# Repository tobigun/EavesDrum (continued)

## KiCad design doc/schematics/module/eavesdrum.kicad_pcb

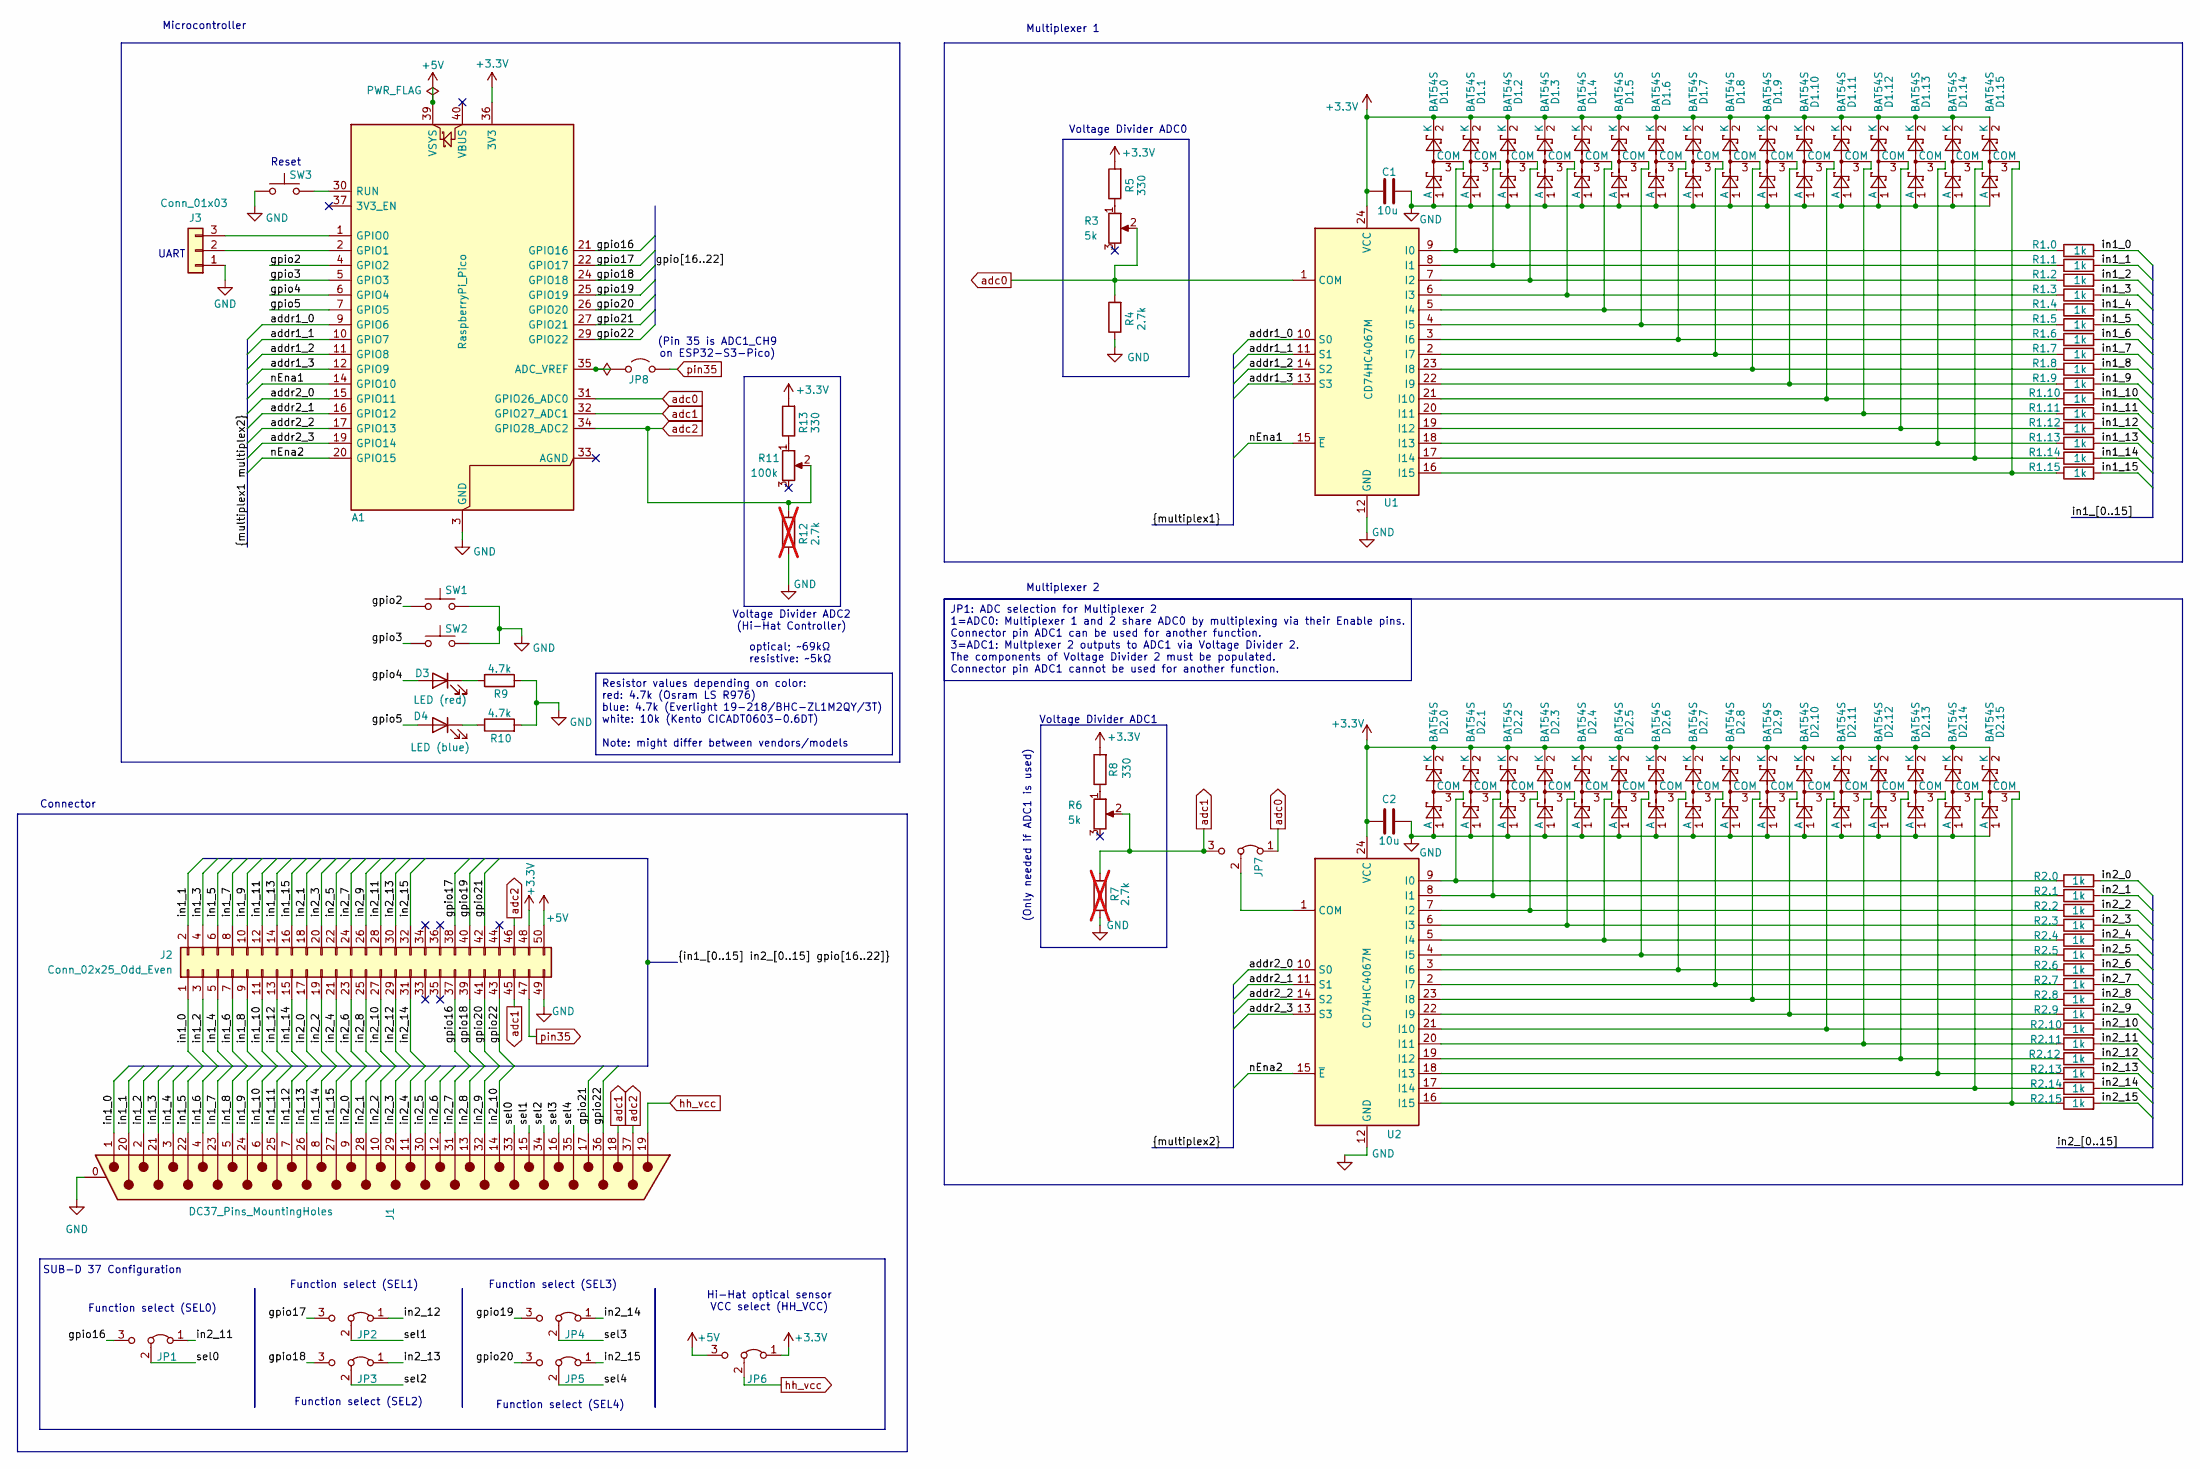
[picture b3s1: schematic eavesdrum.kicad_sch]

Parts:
A1: RaspberryPi_Pico; RaspberryPi_Pico_Common_Unspecified; LCSC C41407547
C1, C2: 10u; C_0805_2012Metric
D1.0, D1.1, D1.2, D1.3, D1.4, D1.5, D1.6, D1.7, D1.8, D1.9, D1.10, D1.11, D1.12, D1.13, D1.14, D1.15, D2.0, D2.1, D2.2, D2.3, D2.4, D2.5, D2.6, D2.7, D2.8, D2.9, D2.10, D2.11, D2.12, D2.13, D2.14, D2.15: BAT54S; SOT-23
D3: LED (red); LED_D3.0mm
D4: LED (blue); LED_D3.0mm
J1: DC37_Pins_MountingHoles; DSUB-37_Pins_Horizontal_P2.77x2.84mm_EdgePinOffset7.70mm_Ho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
J2: Conn_02x25_Odd_Even; IDC-Header_2x25_P2.54mm_Vertical_SMD; LCSC C383615
J3: Conn_01x03; PinSocket_1x03_P2.54mm_Vertical_SMD_Pin1Left
JP1, JP2, JP3, JP4, JP5, JP6: Jumper; PinHeader_1x03_P2.54mm_Vertical_SMD_Pin1Right; LCSC C2875122
JP7: Jumper_3; SolderJumper-3_P1.3mm_Bridged12_RoundedPad1.0x1.5mm_NumberL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
JP8: Jumper_2_Open; SolderJumper-2_P1.3mm_Open_RoundedPad1.0x1.5mm
R1.0, R1.1, R1.2, R1.3, R1.4, R1.5, R1.6, R1.7, R1.8, R1.9, R1.10, R1.11, R1.12, R1.13, R1.14, R1.15, R2.0, R2.1, R2.2, R2.3, R2.4, R2.5, R2.6, R2.7, R2.8, R2.9, R2.10, R2.11, R2.12, R2.13, R2.14, R2.15: 1k; R_0805_2012Metric
R3, R6: 5k; Potentiometer_Bourns_TC33X_Vertical
R4: 2.7k; R_0805_2012Metric
R5, R8, R13: 330; R_0805_2012Metric
R7, R12: 2.7k; R_0805_2012Metric; not fitted
R9, R10: 4.7k; R_0805_2012Metric
R11: 100k; Potentiometer_Bourns_TC33X_Vertical
SW1, SW2, SW3: SW_Push; SW_Push_1P1T_NO_CK_KSC6xxJ
U1: CD74HC4067M; SOIC-24W_7.5x15.4mm_P1.27mm
U2: CD74HC4067M; SOIC-24W_7.5x15.4mm_P1.27mm; LCSC C1545936

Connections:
+3.3V: A1.36 (3V3), C1.1, C2.1, D1.0.2 (K), D1.1.2 (K), D1.2.2 (K), D1.3.2 (K), D1.4.2 (K), D1.5.2 (K), D1.6.2 (K), D1.7.2 (K), D1.8.2 (K), D1.9.2 (K), D1.10.2 (K), D1.11.2 (K), D1.12.2 (K), D1.13.2 (K), D1.14.2 (K), D1.15.2 (K), D2.0.2 (K), D2.1.2 (K), D2.2.2 (K), D2.3.2 (K), D2.4.2 (K), D2.5.2 (K), D2.6.2 (K), D2.7.2 (K), D2.8.2 (K), D2.9.2 (K), D2.10.2 (K), D2.11.2 (K), D2.12.2 (K), D2.13.2 (K), D2.14.2 (K), D2.15.2 (K), J2.48, JP6.1 (A), R5.2, R8.2, R13.2, U1.24 (VCC), U2.24 (VCC)
+5V: A1.39 (VSYS), J2.50, JP6.3 (B)
/addr1_0: A1.9 (GPIO6), U1.10 (S0)
/addr1_1: A1.10 (GPIO7), U1.11 (S1)
/addr1_2: A1.11 (GPIO8), U1.14 (S2)
/addr1_3: A1.12 (GPIO9), U1.13 (S3)
/addr2_0: A1.15 (GPIO11), U2.10 (S0)
/addr2_1: A1.16 (GPIO12), U2.11 (S1)
/addr2_2: A1.17 (GPIO13), U2.14 (S2)
/addr2_3: A1.19 (GPIO14), U2.13 (S3)
/gpio2: A1.4 (GPIO2), SW1.1
/gpio3: A1.5 (GPIO3), SW2.1
/gpio4: A1.6 (GPIO4), D3.2 (A)
/gpio5: A1.7 (GPIO5), D4.2 (A)
/gpio16: A1.21 (GPIO16), J2.37, JP1.3 (B)
/gpio17: A1.22 (GPIO17), J2.38, JP2.3 (B)
/gpio18: A1.24 (GPIO18), J2.39, JP3.3 (B)
/gpio19: A1.25 (GPIO19), J2.40, JP4.3 (B)
/gpio20: A1.26 (GPIO20), J2.41, JP5.3 (B)
/gpio21: A1.27 (GPIO21), J1.17, J2.42
/gpio22: A1.29 (GPIO22), J1.36, J2.43
/in1_0: J1.1, J2.1, R1.0.2
/in1_1: J1.20, J2.2, R1.1.2
/in1_2: J1.2, J2.3, R1.2.2
/in1_3: J1.21, J2.4, R1.3.2
/in1_4: J1.3, J2.5, R1.4.2
/in1_5: J1.22, J2.6, R1.5.2
/in1_6: J1.4, J2.7, R1.6.2
/in1_7: J1.23, J2.8, R1.7.2
/in1_8: J1.5, J2.9, R1.8.2
/in1_9: J1.24, J2.10, R1.9.2
/in1_10: J1.6, J2.11, R1.10.2
/in1_11: J1.25, J2.12, R1.11.2
/in1_12: J1.7, J2.13, R1.12.2
/in1_13: J1.26, J2.14, R1.13.2
/in1_14: J1.8, J2.15, R1.14.2
/in1_15: J1.27, J2.16, R1.15.2
/in2_0: J1.9, J2.17, R2.0.2
/in2_1: J1.28, J2.18, R2.1.2
/in2_2: J1.10, J2.19, R2.2.2
/in2_3: J1.29, J2.20, R2.3.2
/in2_4: J1.11, J2.21, R2.4.2
/in2_5: J1.30, J2.22, R2.5.2
/in2_6: J1.12, J2.23, R2.6.2
/in2_7: J1.31, J2.24, R2.7.2
/in2_8: J1.13, J2.25, R2.8.2
/in2_9: J1.32, J2.26, R2.9.2
/in2_10: J1.14, J2.27, R2.10.2
/in2_11: J2.28, JP1.1 (A), R2.11.2
/in2_12: J2.29, JP2.1 (A), R2.12.2
/in2_13: J2.30, JP3.1 (A), R2.13.2
/in2_14: J2.31, JP4.1 (A), R2.14.2
/in2_15: J2.32, JP5.1 (A), R2.15.2
/nEna1: A1.14 (GPIO10), U1.15 (~E)
/nEna2: A1.20 (GPIO15), U2.15 (~E)
/sel0: J1.33, JP1.2 (C)
/sel1: J1.15, JP2.2 (C)
/sel2: J1.34, JP3.2 (C)
/sel3: J1.16, JP4.2 (C)
/sel4: J1.35, JP5.2 (C)
GND: A1.3 (GND), A1.8 (GND), A1.13 (GND), A1.18 (GND), A1.23 (GND), A1.28 (GND), A1.38 (GND), C1.2, C2.2, D1.0.1 (A), D1.1.1 (A), D1.2.1 (A), D1.3.1 (A), D1.4.1 (A), D1.5.1 (A), D1.6.1 (A), D1.7.1 (A), D1.8.1 (A), D1.9.1 (A), D1.10.1 (A), D1.11.1 (A), D1.12.1 (A), D1.13.1 (A), D1.14.1 (A), D1.15.1 (A), D2.0.1 (A), D2.1.1 (A), D2.2.1 (A), D2.3.1 (A), D2.4.1 (A), D2.5.1 (A), D2.6.1 (A), D2.7.1 (A), D2.8.1 (A), D2.9.1 (A), D2.10.1 (A), D2.11.1 (A), D2.12.1 (A), D2.13.1 (A), D2.14.1 (A), D2.15.1 (A), J1.0 (PAD), J2.49, J3.1, R4.1, R7.1, R9.2, R10.2, R12.1, SW1.2, SW2.2, SW3.1, U1.12 (GND), U2.12 (GND)
unnamed: A1.35 (ADC_VREF), JP8.1 (A)
unnamed: A1.1 (GPIO0), J3.3
unnamed: A1.2 (GPIO1), J3.2
unnamed: A1.30 (RUN), SW3.2
unnamed: D1.0.3 (COM), R1.0.1, U1.9 (I0)
unnamed: D1.1.3 (COM), R1.1.1, U1.8 (I1)
unnamed: D1.2.3 (COM), R1.2.1, U1.7 (I2)
unnamed: D1.3.3 (COM), R1.3.1, U1.6 (I3)
unnamed: D1.4.3 (COM), R1.4.1, U1.5 (I4)
unnamed: D1.5.3 (COM), R1.5.1, U1.4 (I5)
unnamed: D1.6.3 (COM), R1.6.1, U1.3 (I6)
unnamed: D1.7.3 (COM), R1.7.1, U1.2 (I7)
unnamed: D1.8.3 (COM), R1.8.1, U1.23 (I8)
unnamed: D1.9.3 (COM), R1.9.1, U1.22 (I9)
unnamed: D1.10.3 (COM), R1.10.1, U1.21 (I10)
unnamed: D1.11.3 (COM), R1.11.1, U1.20 (I11)
unnamed: D1.12.3 (COM), R1.12.1, U1.19 (I12)
unnamed: D1.13.3 (COM), R1.13.1, U1.18 (I13)
unnamed: D1.14.3 (COM), R1.14.1, U1.17 (I14)
unnamed: D1.15.3 (COM), R1.15.1, U1.16 (I15)
unnamed: D2.0.3 (COM), R2.0.1, U2.9 (I0)
unnamed: D2.1.3 (COM), R2.1.1, U2.8 (I1)
unnamed: D2.2.3 (COM), R2.2.1, U2.7 (I2)
unnamed: D2.3.3 (COM), R2.3.1, U2.6 (I3)
unnamed: D2.4.3 (COM), R2.4.1, U2.5 (I4)
unnamed: D2.5.3 (COM), R2.5.1, U2.4 (I5)
unnamed: D2.6.3 (COM), R2.6.1, U2.3 (I6)
unnamed: D2.7.3 (COM), R2.7.1, U2.2 (I7)
unnamed: D2.8.3 (COM), R2.8.1, U2.23 (I8)
unnamed: D2.9.3 (COM), R2.9.1, U2.22 (I9)
unnamed: D2.10.3 (COM), R2.10.1, U2.21 (I10)
unnamed: D2.11.3 (COM), R2.11.1, U2.20 (I11)
unnamed: D2.12.3 (COM), R2.12.1, U2.19 (I12)
unnamed: D2.13.3 (COM), R2.13.1, U2.18 (I13)
unnamed: D2.14.3 (COM), R2.14.1, U2.17 (I14)
unnamed: D2.15.3 (COM), R2.15.1, U2.16 (I15)
unnamed: D3.1 (K), R9.1
unnamed: D4.1 (K), R10.1
unnamed: JP7.2 (C), U2.1 (COM)
unnamed: R3.1, R5.1
unnamed: R6.1, R8.1
unnamed: R11.1, R13.1
adc0: A1.31 (GPIO26_ADC0), JP7.1 (A), R3.2, R4.2, U1.1 (COM)
adc1: A1.32 (GPIO27_ADC1), J1.18, J2.45, JP7.3 (B), R6.2, R7.2
adc2: A1.34 (GPIO28_ADC2), J1.37, J2.46, R11.2, R12.2
hh_vcc: J1.19, JP6.2 (C)
pin35: J2.47, JP8.2 (B)

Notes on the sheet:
Microcontroller
Multiplexer 2
optical; ~69kΩ resistive: ~5kΩ
Function select (SEL3)
Connector
Function select (SEL0)
UART
Function select (SEL2)
SUB-D 37 Configuration
(Pin 35 is ADC1_CH9 on ESP32-S3-Pico)
Voltage Divider ADC2 (Hi-Hat Controller)
Multiplexer 1
Voltage Divider ADC1
Function select (SEL4)
Voltage Divider ADC0
(Only needed if ADC1 is used)
Function select (SEL1)
Reset
Hi-Hat optical sensor VCC select (HH_VCC)
Resistor values depending on color: red: 4.7k (Osram LS R976) blue: 4.7k (Everlight 19-218/BHC-ZL1M2QY/3T) white: 10k (Kento CICADT0603-0.6DT) Note: might differ between vendors/models
JP1: ADC selection for Multiplexer 2 1=ADC0: Multiplexer 1 and 2 share ADC0 by multiplexing via their Enable pins. Connector pin ADC1 can be used for another function. 3=ADC1: Multplexer 2 outputs to ADC1 via Voltage Divider 2. The components of Voltage Divider 2 must be populated. Connector pin AD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

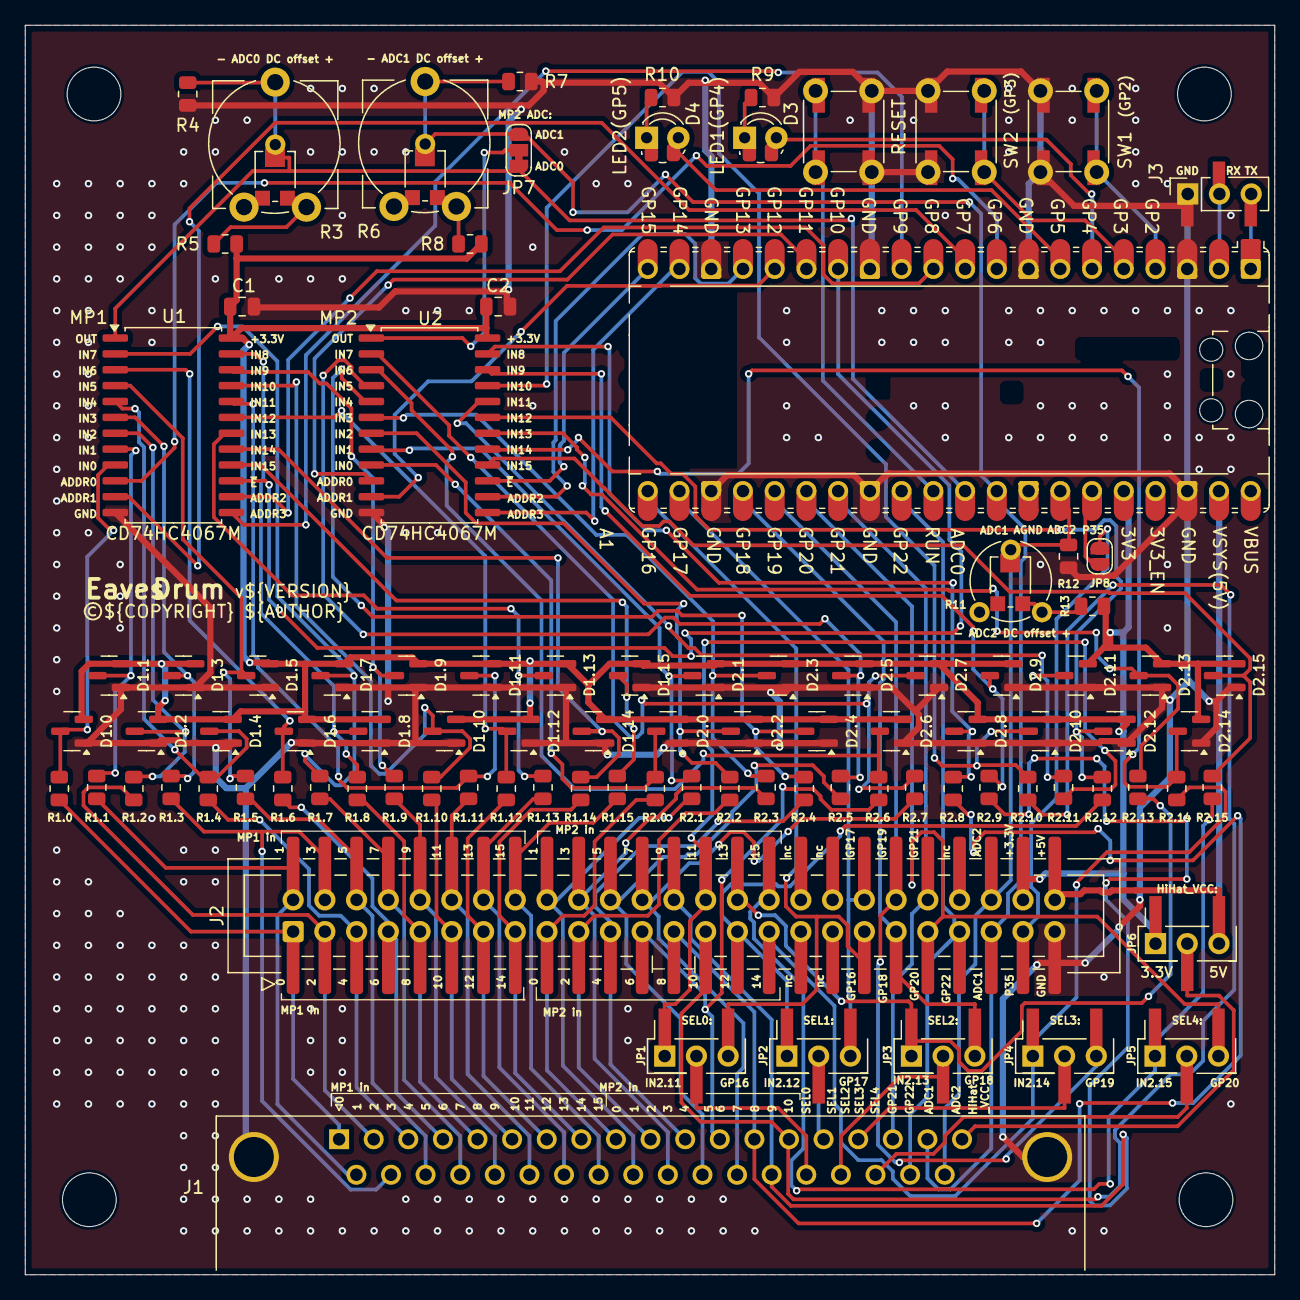
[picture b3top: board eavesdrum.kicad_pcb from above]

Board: 2 copper layers, 100.0 x 100.0 mm, 100 parts (0 on the bottom side), 108 nets.

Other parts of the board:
M4_1, M4_2, M4_3, M4_4: MountingHole_4.3mm_M4

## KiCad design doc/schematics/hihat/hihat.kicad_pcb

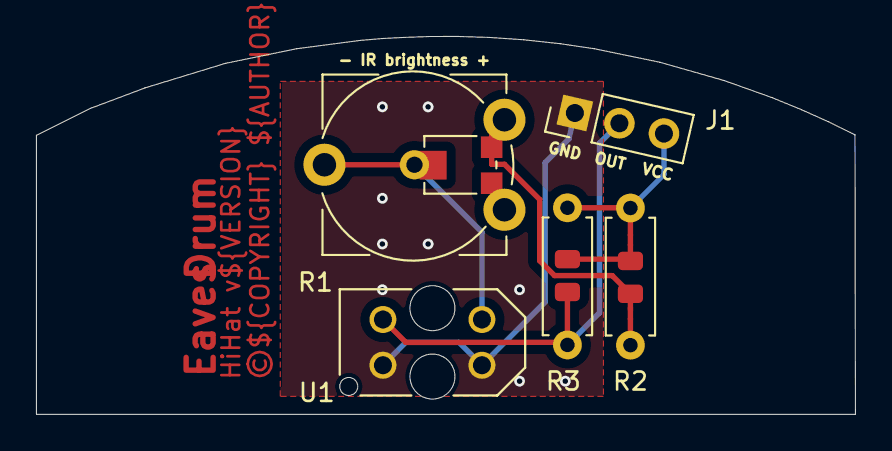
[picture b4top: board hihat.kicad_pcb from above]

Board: 2 copper layers, 45.5 x 21.0 mm, 7 parts (0 on the bottom side), 5 nets.

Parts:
J1: Conn_01x03; PinHeader_1x03_P2.54mm_Vertical
M3_1, M3_2: MountingHole_3.2mm_M3
R1: 5k; Potentiometer_ACP_CA9-VSMD_Vertical
R2: 100; R_Axial_DIN0207_L6.3mm_D2.5mm_P7.62mm_Horizontal
R3: 10k; R_Axial_DIN0207_L6.3mm_D2.5mm_P7.62mm_Horizontal
U1: TCRT5000; tcrt5000

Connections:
/sens_out: J1.2, R3.2, U1.COLL
GND: J1.1, U1.CATH, U1.E
unnamed: R1.1, R2.1
unnamed: R1.2, U1.A
VCC: J1.3, R2.2, R3.1

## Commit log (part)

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2025-08-03 use absolut imports
2025-08-03 move settings to pad again
2025-08-04 update esp32
2025-08-05 adjust hihat schematic
2025-08-05 adjust module schematics
2025-08-06 fix pcba issues
2025-08-06 update esp32 sdk
2025-08-06 add schema for config
2025-08-06 move mappings
2025-08-06 add mapping for ezdrummer
2025-08-07 add mappings
2025-08-07 move presets
2025-08-30 update resistor values
2025-08-30 update pico arduino
2025-08-30 update usb descriptor
2025-08-30 reset usb on boot and perform led test
2025-09-07 uodate dependencies
2025-09-07 add undefined mapping value and move mappings out of pad
2025-09-07 remove pedal chick flag
2025-09-07 check for tinyusb
2025-09-07 disable unimplemented cross note detection in ui
2025-09-07 fix TODO
2025-09-07 check for padIndex in cross-stick
2025-09-07 show unused mappings
2025-09-07 fix dirty flag
2025-09-07 make connector selectable via ui
2025-09-07 handle invalid roles
2025-09-08 make roles and names editable
2025-09-08 add pad type selector to mappings
2025-09-08 reformat role
2025-09-08 improve representation of roles
2025-09-09 cleanup ediztable header
2025-09-10 make role names configurable
2025-09-11 reset mappings if mappings file is uploaded
2025-09-12 configs can be replaced via ui now
2025-09-17 fix ambiguous initialization
2025-09-17 update vite
2025-09-22 add cymbal 3+4 and tom 4+5
2025-09-23 fix pedal by inversion
2025-09-23 fine-tune config
2025-09-23 add more debug output
2025-09-24 reformat config to match UI format
2025-09-24 handle config download in ui
2025-09-24 validate uploads
2025-09-24 flush muxers on demand
2025-09-26 add missing license
2025-09-26 update spice model
2025-09-26 do not flush mux if simulated
2025-09-26 add missing restriction for choke type
2025-09-27 update documentation
2025-09-27 Update README.md
    fix important section
2025-09-27 add more results
2025-09-27 more readme
2025-09-27 fix spelling
2025-09-27 fix grammar
2025-09-27 fix style
2025-09-27 update presets
2025-09-27 update docu
2025-09-27 change figure labels
2025-09-28 replace schema url
2025-09-28 fix images
2025-09-28 More fixes
2025-09-28 try to fix indentation
2025-09-28 embed font into logo
2025-09-28 replace favicon
2025-09-28 show error message if resource is not found
2025-09-28 abort on error
2025-09-28 fix build pipeline
2025-09-29 replace erlang uf2tool with python script
2025-09-29 update pio pico
2025-09-29 switch order of fs and fw in uf2 file to fix pico1 issues with missing ui
2025-09-29 finalize build
2025-09-29 set version to 1.0.0
2025-09-29 add hihat instructions
2025-09-30 add github pages config
2025-09-30 update pages
2025-09-30 add plugins
2025-09-30 readd includes dir
2025-09-30 update github pages
2025-09-30 update github
2025-09-30 fiw md links
2025-10-02 change unsupported info to note
2025-10-09 add info about me
2025-10-12 add more latency results
2025-10-19 update to newest pico framework
2025-10-19 keep config after flashing new fw
2025-11-12 Add YouTube trailer link to README
    Added a YouTube trailer link to the README.
2025-11-16 module schematic v1.1.1: use header instead of pico
2025-11-16 add efnote pinout
2025-11-16 rename module schematics
2025-11-17 fix link to schematics
2025-11-17 fix anchor
2026-02-01 Update issue templates
2026-03-06 update libraries
2026-03-06 add bt midi lib
2026-03-09 add debug macro to ble_midi
2026-03-09 disable usage cyw43 led
2026-03-10 update ui deps
2026-03-15 add support for midi output modes
2026-03-16 add support for ble server
2026-03-17 centralize access to serial port
2026-03-17 fix wireless model detection
2026-03-20 bugfixes
2026-03-20 support for 5-pin din Midi and Guitar Hero Drums
2026-03-20 improve text for section for "Pads with undefined Roles"
2026-03-21 move ble client update method to ble midi transport update
2026-03-21 add support for wifi network
2026-03-21 use Ble LED for Midi connection in general
2026-03-21 replace watchdog LED with watchdog timer
2026-03-21 rename usb to usb client
2026-03-22 poll usb device task manually
2026-03-22 ckeanup io
2026-03-22 add USB-Host Midi
2026-03-22 cleanup
2026-03-22 cleanup esp32
2026-03-22 correct LED polarity
2026-03-22 fix endless loop in midi transport
2026-03-22 map din serial to expansion slot
2026-03-22 fix USB host crashes
2026-03-22 try to fix USB Host freezes
2026-03-22 fix unit tests
2026-03-22 update github flow actions
2026-03-22 add pico2w
2026-03-23 remove picow: does not have enough RAM for parsing yaml
2026-03-23 disable picow
2026-03-23 implement panic in AsyncTCP
2026-03-23 Bugfix #5: fix config upload discarded if config is sent in multiple chunks
2026-03-23 add PICO-PIO to licenses
2026-03-23 stabilize usb network connection
2026-03-23 reduce warnings during test
2026-03-23 fix native build and cleanup WS handling
2026-03-23 cache esp32 build
2026-03-23 github actions: require cache name
2026-03-23 use stock lwip
2026-03-23 update ArduinoJson
2026-03-23 update yamlduino
2026-03-23 update platform pico
2026-03-23 move networking to lib folder
2026-03-25 rename base circuit schematics
2026-03-25 add connector schematics
2026-03-25 schematics for module 1.2
2026-03-26 update schematics
2026-03-26 move schematics
2026-03-26 add note for revision 1.2
2026-03-27 minor schematic change
2026-03-27 update gitignore
2026-03-28 make sure a even single points (in between gaps) in the graph are visible
2026-03-28 move touch code
2026-03-30 add touch support
2026-03-30 tinyusb networking is used as a lib now
2026-03-30 embed jsonc as resource
2026-03-30 improve documentation
2026-03-30 fix esp32 and native build
2026-03-31 update touch
2026-04-01 add banner for Europe Drum Show
2026-04-02 add efnote conenctor pinout
2026-04-03 add more statistics
2026-04-03 fix build
2026-04-03 move general config to own file
2026-04-03 add board version
2026-04-03 copy SerialUART for TX only Serial
2026-04-03 rename
2026-04-03 Do not use RX pin for MIDI Serial
2026-04-03 select MIDI TX pin depending on board version
2026-04-03 fix readme
2026-04-03 fix board version loading
2026-04-04 add shirt svg
2026-04-04 fix json schema
2026-04-04 fix statistics texts
2026-04-05 try to fix banner
2026-04-05 fix banner
2026-04-05 tested with iOS
2026-04-05 change choke types according to pad type
2026-04-05 update schema version
2026-04-05 avoid intepretation of board version as number
2026-04-06 move board specific files
2026-04-06 change readme for board 1.2
2026-04-06 use board 1.1 as default
2026-04-06 fix watchdog due to non-stopping BLE server
2026-04-06 add support for touch choke for piezo cymbals
2026-04-07 add latency measurements for focusrite scarlett
2026-04-07 prepare for decay time support
2026-04-08 add mapping for superior drummer
2026-04-10 remove unneccessary holes for jack connector
2026-04-14 remove link to drum show
2026-04-17 cleanup for board v1.2
2026-04-18 add info about connector PCB
2026-04-18 link connector schematics
2026-04-18 default config to hardware v1.2
2026-04-26 set version to 1.1.0
2026-04-26 Fix naming of "USB Device" in UI
2026-05-17 Refine Bluetooth LE Server section in README
    Removed redundant text and clarified BLE Server mode usage for Windows.
2026-05-26 wiimote-lib: add support for guitar hero drums
2026-05-26 pico: support more buttons
2026-05-26 increase flush time as bt classic takes quite long to send interrupts
2026-05-26 add wiimote-lib from Loc15/PicoGamepadConverter
2026-05-26 add raw log level (for logging in external libs to DebugSerial)
2026-05-26 fix wrong log levels in ui
2026-05-26 remove ble_midi_server.h from header to avoid conflicting hid definitions (ble vs usb)
2026-05-26 rename midi transport gh to gh spi
2026-05-26 add used libraries section to readme
2026-05-26 add support for wii guitar hero drum
2026-05-26 fix and stabilize wiimote-lib
2026-05-26 use ATTR_PACKED macro
2026-05-26 move usb host code to own file
2026-05-26 remove redundant noInterrupts call from config mapper
    This is already called by the flash library
2026-05-26 add support for USB Host HID gamepads
2026-05-27 support for wii rockband drums
2026-05-28 unify device name handling for HID and MIDI USB Host mode
2026-05-30 try to fix jekyll build
2026-06-02 share mapping between all GH/RB variants
2026-06-03 add generic gamepad mode
2026-06-07 fix: send monitor data of previous hit if new hit detected
2026-06-07 ui: make year a pattern in copyright notice
2026-06-07 Add decay phase
2026-06-07 use max value during scan time in decay curve instead of hit value
2026-06-17 fix closed notes
2026-06-17 add decayTimeMs/decayType to jsonc
2026-06-17 add FAQ
